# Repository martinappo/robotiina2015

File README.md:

Robotiina
=========

Robotex 2014 participant 

##How to build:
###Under windows

* Install Visual Studo 2013 express
* Download OpenCV **2.4.9** and unpack into **c:\** drive 
 *  check that *C:\opencv\build\include* paths exist
 *  check that *C:\opencv\build\x86\vc12\lib* path exists
 *  check that *C:\opencv\build\x86\vc12\bin* path exists
* Download Boost binaries for VS2013 
 *  http://sourceforge.net/projects/boost/files/boost-binaries/1.56.0/ 
 *  **boost_1_56_0-msvc-12.0-32.exe**
 *  install into **C:\boost_1_56_0**
 *  check that *C:\boost_1_56_0\boost* path exists
 *  check that *C:\boost_1_56_0\lib32-msvc-12.0* path exists
* clone this project and compile it
* start robotiina.bat to launch it or launch it form IDE

###On Linux (Ubuntu/jessie)

* install cmake, gcc and git
 * sudo apt-get install build-essential cmake git 
* install ximea sdk
 * dowload sdk (XIMEA_Linux_SP.tgz) from http://www.ximea.com/support/documents/4
  * wget http://www.ximea.com/support/attachments/271/XIMEA_Linux_SP.tgz
  * tar -zxvf XIMEA_Linux_SP.tgz
  * cd package/
  * ./install -cam_usb30
* install  opencv 3.0.0
  * install gtk+2
    * sudo apt-get install libgtk2.0-dev
  * download latest opencv 3
    * wget https://github.com/Itseez/opencv/archive/3.0.0.zip
    * unzip 3.0.0.zip
    * cd opencv-3.0.0/
  * build using cmake
    * mkdir opencv-3.0.0
    * cd opencv-3.0.0/ 
    * cmake -D WITH_XIMEA=YES -D CMAKE_BUILD_TYPE=RELEASE -DCMAKE_INSTALL_PREFIX:PATH=/usr ..
    * make
  * install using checkinstall
    * sudo apt-get install checkinstall
    * sudo checkinstall
* install boost >= 1.55.0
 * sudo apt-get install libboost-all-dev
* clone repro
 * git clone https://github.com/martinappo/robotiina2015
 * cd robotiina2015
* run cmake .
* run make
* to start program execute ./robotiina

###On Rasperry Pi 2
* make sure you upgrade to jessie
 * Update /etc/apt/sources.list to have jessie wherever you've currently got wheezy
 * sudo apt-get update
 * sudo apt-get dist-upgrade
 * sudo rpi-update
 * reboot
* check that gcc version > 4.8
* follow linux instructions
* To use camera make sure /dev/video0 is present
 * "sudo modprobe bcm2835-v4l2" if driver not loaded

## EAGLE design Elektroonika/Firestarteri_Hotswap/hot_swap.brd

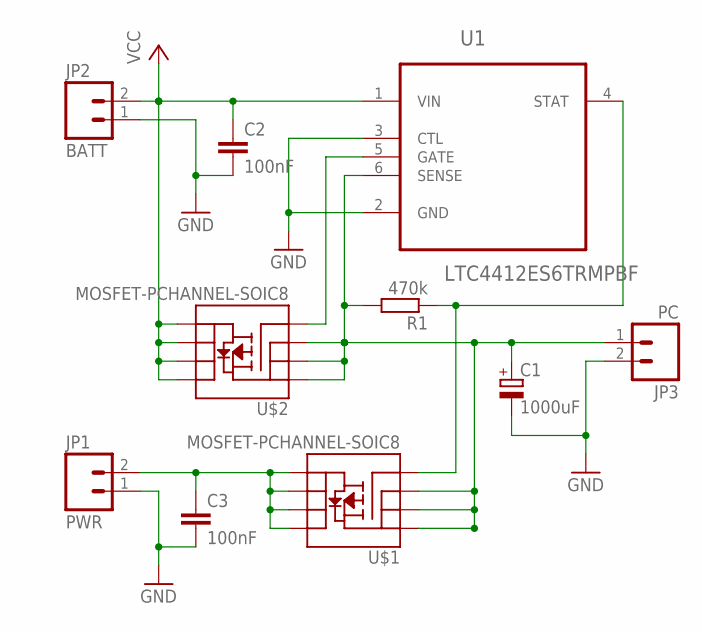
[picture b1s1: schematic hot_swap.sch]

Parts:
C1: 1000uF; E3,5-8
C2, C3: 100nF; C0603K
JP1: PWR; SCREWTERMINAL-3.5MM-2
JP2: BATT; SCREWTERMINAL-3.5MM-2
JP3: PC; SCREWTERMINAL-3.5MM-2
R1: 470k; R0603
U1: LTC4412ES6TRMPBF; SOT95P280X100-6N
U$1, U$2: MOSFET-PCHANNEL-SOIC8; SO08

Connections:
GND: C1.-, C2.2, C3.2, JP1.1, JP2.1, JP3.2, U1.2 (GND), U1.3 (CTL)
unnamed: C1.+, JP3.1, R1.2, U1.6 (SENSE), U$1.1 (S), U$1.2 (S), U$1.3 (S), U$2.1 (S), U$2.2 (S), U$2.3 (S)
unnamed: U1.5 (GATE), U$2.4 (G)
unnamed: R1.1, U1.4 (STAT), U$1.4 (G)
VCC: C2.1, JP2.2, U1.1 (VIN), U$2.5 (D), U$2.6 (D), U$2.7 (D), U$2.8 (D)
VCC2: C3.1, JP1.2, U$1.5 (D), U$1.6 (D), U$1.7 (D), U$1.8 (D)

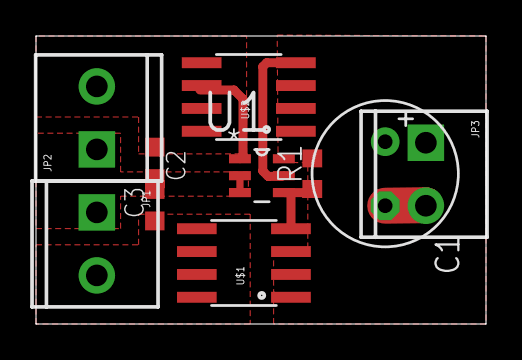
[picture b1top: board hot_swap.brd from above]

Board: 2 copper layers, 25.0 x 16.0 mm, 10 parts (0 on the bottom side), 6 nets.

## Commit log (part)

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2015-09-16 crash fix
    and distinct object name from thread name
2015-09-16 display size almost dynamic
2015-09-16 angles in doubles
2015-09-17 new feature: program size from command line option
2015-09-18 inrange asenduse test
2015-09-18 try nr2
2015-09-18 simd principle used
    http://sci.tuomastonteri.fi/programming/sse
2015-09-18 imagethresholders into seaparate classes/files
2015-09-18 opencv pallarer for
2015-09-18 custom inRange finally working fast
2015-09-19 angles from robot, not from gates
2015-09-19 Fixed robot direction and centerline calculations.
2015-09-19 Improved robot direction calculation.
2015-09-20 Object Y axis values on soccer field were inverted - Y grows downwards.
2015-09-21 Changed goal position from whole detected object centre to closest side centre.
2015-09-23 more points for distance calibration
2015-09-23 nonstretched camera image is back + avoid crash
2015-09-24 robot positioning improvements
    y = 13,136e^0,008x
2015-09-24 gates with brighter color
2015-09-24 polynomial fuction for finding distance
2015-09-25 robot position fixes
2015-09-25 rotated videos
2015-09-25 calibration data update
2015-09-26 typo in robot pos calc
2015-09-27 Cropping added to color calibration
2015-09-27 kalman filter added to robot position
2015-09-28 balls are still lost
2015-09-28 ups on copy/paste
2015-09-28 balls are back but they swap places
2015-09-28 cleanup
2015-09-29 minor improvements
2015-10-01 naive version of finding close balls
2015-10-01 Removed StillCamera class: https://github.com/martinappo/robotiina2015/issues/16
2015-10-01 Added explicit castings to remove compiler warnings v2.
2015-10-04 emty sim working
2015-10-04 avoid crash
2015-10-04 progress
2015-10-04 ball distance fixed
2015-10-04 simulate rotation
2015-10-04 not so easy
2015-10-04 angles fixed
2015-10-05 smooth manual control
2015-10-05 remove flickering
2015-10-05 gates little larger
2015-10-06 not quite working
2015-10-09 Fixed gateselection (could be nicer) and got autopilot to start
2015-10-10 Fixes to autopilot.
2015-10-11 show simulation positions on screen
2015-10-11 simulation sort of working with manual control
2015-10-11 made test autopilot to work
2015-10-12 autopilot is catching balls
2015-10-13 Commented out obsolete LOCATE_GATE. Changed field length in RobotPosition.cpp from 450 to 460 & GatePosition coordinates 225 -> 230.
2015-10-13 coilgun simulator
2015-10-13 reversed manualcontrol directions
2015-10-18 Commented out spam logging
2015-10-18 Going back from test autopilot not enabling autopilot
2015-10-18 Basic 'drive to ball' logic
2015-10-18 added FPS counter to simulator
2015-10-19 simulator driving fixed
2015-10-19 Autopilot drive() input angle converted from degrees to radians.
2015-10-20 correction in speed
2015-10-20 Everything
2015-10-20 Aim gate improvements
2015-10-21 ball heading fixed, but still kicks in wrong direction
2015-10-21 Ball movement improved, autopilot speeds increased.
2015-10-21 Re-enabled and improved small distance ball management.
2015-10-21 do not kick after timeout
2015-10-21 rotate while moving
2015-10-21 Andres' work v2
2015-10-22 Drive home implemented
2015-10-24 Initial 2v2 added to newAutoPilot. Added drivemodes: DRIVEMODE_2V2_OFFENSIVE, DRIVEMODE_2V2_DEFENSIVE, DRIVEMODE_2V2_KICKOFF, DRIVEMODE_2V2_AIM_GATE, DRIVEMODE_2V2_KICK, DRIVEMODE_2V2_DRIVE_TO_BALL, 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
2015-10-27 NewAutoPilot refactoring. New methods: bool aimTarget(ObjectPosition &target, double errorMargin = 10); bool driveToTarget(ObjectPosition &target, double maxDistance = 20); BallPosition getClosestBal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
2015-10-27 driveToTargetWithAngle() implemented as an alternative to more precise aiming and straight driving. bool USE_ANGLE_DRIVING added for easy switching between 2 driving modes.
2015-10-27 filter new project files into folders
2015-10-27 2vs2 gameplay support
2015-10-27 getClosestBall fix
2015-10-27 SImulator dribbler update.
2015-10-29 udp communication
2015-10-29 sim broadcast
2015-10-29 simulator communication is working
2015-10-29 window size smaller
2015-10-29 simulator communication improved
2015-10-30 balls over network
2015-10-30 ball y coordinate fixed
2015-10-30 improvements
2015-10-30 Added communication module for referee commands
2015-10-31 slave kicking
2015-10-31 Made referee module more fool proof. now working without hardware
2015-10-31 Local referee command giving functionality. Acting for start and stop commands
2015-10-31 better async serial
2015-10-31 referee -> fieldstate communication
2015-11-01 Robot's communication copy-pasta from simulator to soccerfield
2015-11-01 made conf module to work with ref module settings
2015-11-01 Using fieldstate and gamemode directly from ref module
2015-11-02 2vs2 states moved to muiltimode play module
2015-11-02 minor sideeffects fixed
2015-11-02 2V2 opponent kickoff/free kick/free throw
2015-11-03 revert new ballarray usage
2015-11-03 single ball game for 2vs2
2015-11-03 not working
2015-11-03 dummy allly pos & kick with force
2015-11-04 referee simulator
2015-11-04 cleanup again
2015-11-04 doh, more cleanup
2015-11-04 2vs2 changes
2015-11-04 working wheelcontroller
2015-11-04 check simulator robot id many times
2015-11-04 Stop motors on stop, stop motors on loation, MultiMode fixes
2015-11-05 refcom message handling to base class
2015-11-05 simulator inherits form commodule + typo fix
2015-11-05 remove wheelsimulator
2015-11-06 show robot id-s in main screen
2015-11-08 4 wheeled robot
2015-11-09 opencv 3 instructions
2015-11-10 cam and com port fixes
2015-11-10 wheel id's from 1...4
2015-11-11 something
2015-11-11 Made coil and wheels use the same port
2015-11-12 live changes
2015-11-14 simulator uses com port communication
2015-11-15 desctructor was not called
2015-11-18 capitalize stuff
2015-11-18 debug stuff
2015-11-18 testing
2015-11-18 live changes @nuc
2015-11-18 some shangec
2015-11-19 matrices
2015-11-19 wheel calc fixed
2015-11-19 serial loging + again something
2015-11-19 why not rotating?
2015-11-20 fix messup
2015-11-20 sleep after creating serial comm
2015-11-20 sim wheels intialized
2015-11-20 simulator back in action
2015-11-20 dialog thread safety improved
2015-11-20 live changes again
2015-11-20 unitialized var
2015-11-20 logging
2015-11-20 fix debug
2015-11-20 Night debugging
2015-11-20 improve me not
2015-11-20 serial read back
2015-11-20 Removed threadedclass from refcom.
2015-11-20 serial is fixing
2015-11-20 fabs
2015-11-20 ball in tribbler is working
2015-11-21 better code for everyone
2015-11-21 AimGate for kick angle error margin dependant on gate distance.
2015-11-21 Typo fix
2015-11-21 commented io.reset
2015-11-23 Autocalibrator parameters tweaking.
2015-11-23 Keyboard buttons working again.
2015-11-23 multiple fixes + robot pos using kalman filter
2015-11-23 closest ball + flip angles along y-axis
2015-11-24 virtual flip
2015-11-24 hardcore flip restored and old videos replaced
2015-11-24 better flipping
2015-11-24 no need to rotate balls in Frontcamera vision
    but they must be rotated in updateFieldCoords
2015-11-24 Threadless WheelController init.
2015-11-24 ximea cliping
2015-11-25 bumpy mirrot calib
2015-11-25 simulator back to business
2015-11-25 goal in simulator
2015-11-25 lot of changes that break everything
2015-11-25 comment out logging
2015-11-26 draw field borders in simulator
2015-11-26 and centre circle
2015-11-26 crash fix (hopefully)
2015-11-26 ballInTribbler rewritten
2015-11-26 simulator fixed (maybe)
2015-11-27 somewhat working code
2015-11-27 back to where we started
2015-11-27 Removed unused code. OS checks
2015-11-27 improved aiming
2015-11-27 Removed some warnings. Fixed a bug maybe
2015-11-28 DriveToBall::stepAimGate
2015-11-28 bug fix vol2.
2015-11-29 okayish_football_play
2015-11-29 fixed some things
2015-11-29 RotateAroundBall
2015-11-29 maybe
2015-11-30 tribblercheck
2015-11-30 kalman filter closest ball
2015-11-30 fixes
2015-11-30 probably broke everything
2015-11-30 some thoughts
2015-11-30 balls back to sim
2015-12-01 unitialized variable
2015-12-01 auto white balance off
2015-12-01 the_fix_that_broke_everything
2015-12-01 distance cal
2015-12-01 fixes (hopefully)
2015-12-01 mask out balls in gate
2015-12-01 MultiPlay driveToBall and simulator robots drawing
2015-12-01 dumb pass
2015-12-01 findclosest ball refactor and check border
2015-12-01 aim on catch
2015-12-01 Partner position determining.
2015-12-01 robot color setting
2015-12-02 collision detection
2015-12-02 multiplay mode changes
2015-12-02 little more collison things
2015-12-02 vtec kicking in
2015-12-02 collision detection detected
2015-12-02 localChanges
2015-12-02 2v2Tweaks
2015-12-02 dummy crash state
2015-12-02 more2v2Offensive
2015-12-02 crash test
2015-12-02 rotateAroundBall_ballInTribblerCheck
2015-12-02 do not kick on start
2015-12-02 catchBall
2015-12-02 Using start as a flag not separate gamestate
2015-12-02 better collision detection
2015-12-02 thingsBeBetterMaybe
2015-12-03 Mostly just cleanup
2015-12-03 collision detection might be better
2015-12-03 collison wider
2015-12-03 collision detectio on/off
2015-12-03 collison again
2015-12-03 BallCatcher
2015-12-03 Non-behavioural change to catchBall(s) + cleanup&refactoring
2015-12-03 ball behind border vol2
2015-12-03 mask self on border detection
2015-12-03 stuff
2015-12-03 objects near ball
2015-12-03 drivemode change
2015-12-03 simulator fixed
2015-12-03 balls back
2015-12-03 no balls crash fix & drive home
2015-12-03 multimode play
2015-12-04 Better crash fix maybe
2015-12-04 communication between partners
2015-12-04 kickoff
2015-12-04 ballintrib
2015-12-04 Kalman filter
2015-12-04 Better filtering
2015-12-04 2V2 goal keeper
2015-12-04 catch
2015-12-04 state mixup
2015-12-04 More filter fixes
2015-12-04 filter upgrade
2015-12-04 RobotDetection (maybe working)
2015-12-04 initial goalkeeping
2015-12-04 robot detection
2015-12-04 Stop rotation on q
2015-12-04 crash detection
2015-12-04 Another version of goalkeeping
2015-12-04 BallInTribblerTime implemented
2015-12-04 Filter again
2015-12-04 Goalkeeper vol3
2015-12-04 Filter
2015-12-04 Goalkeeping vol 9000
2015-12-04 filter calibration
2015-12-04 print test states
2015-12-04 Exclude useless stuff
2015-12-04 Big commit
2015-12-04 naive drive to ball on kicoff
2015-12-04 bug fix
2015-12-04 HideUseless setting
2015-12-04 fix the fix
2015-12-04 rews
2015-12-04 UseKalmanFilter setting
2015-12-04 Manuel Neuer
2015-12-04 Improved goalkeeping
2015-12-04 Wait before reporting ball missing from tribbler
2015-12-04 naive drive
2015-12-04 Speed to 0 in testmode after state change
2015-12-04 Drive to ball gate 2v2
2015-12-04 Gate corner detection
2015-12-04 other ball in tribbler visible
2015-12-05 ball in tribbler 300ms delay
2015-12-05 Fixed no ball distance
2015-12-05 tribbler speed can be set any repeatedly
2015-12-05 fixed merge gates
2015-12-05 Goalkeep vol 3:15
2015-12-05 things
2015-12-05 threadless statemachine
2015-12-05 mjau
2015-12-05 opponent kicks
2015-12-05 balls in tribbler
2015-12-05 decoy
2015-12-05 Goal keeper messages. Also - StateMachine broken - newMode uninited.
2015-12-05 newMode init restored in THREADLESS_STATREMACHINE
2015-12-05 CatchBall stuck in state gamemode check + cleanup
2015-12-05 Master to become decoy after our kickoff. + refactoring.
2015-12-05 Increased ball movement detection margins and added alternative defensive.
2015-12-05 fix2
2015-12-05 alternative defense in use
2015-12-05 Threadful stateMachine
2015-12-05 state machine fix?
2015-12-05 Revert "merge two largest contours"
    This reverts commit 68bddc36442159b706d802c4b2263936abb7bf0e.
2015-12-05 Closest corners out. Stop tribbler on ref stop
2015-12-05 driveHomeAtStart
2015-12-05 First steps to obstruction detection
2015-12-05 moreDriveHome
2015-12-05 driveHomeDribblerCheck
2015-12-05 Revert "Filtering real cartesian coords. Possibly ruining filter."
    This reverts commit 4dd574dc37a4087b9ad0a3dcb5ee403d36abc7f6.
2015-12-05 Detect obstruction
2015-12-05 betteAiming?
2015-12-05 FILTEEEER
2015-12-05 more filter
2015-12-06 Dodge obstruction
2015-12-06 Just shoot when near
2015-12-06 Drive_home recgognize balls.
2015-12-06 kicking fix
2015-12-06 merge
2015-12-06 getBall include heading try.
2015-12-06 filter gates

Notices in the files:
parts and their libraries:
SparkFun: Licensing: CC v3.0 Share-Alike You are welcome to use this library for commercial purposes.
